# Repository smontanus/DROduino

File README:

DROduino
--------
DROduino is a prototype Digital ReadOut (DRO) system designed specifically for the
Taig Mini-Lathe. It is based on the Arduino UNO development board and utilizes high
resolution encoders to capture tool movement.

Author
------
Stephen S. Montanus
email: smont3780@gmail.com

License
-------
Creative Commons Attribution-ShareAlike 4.0 International Public License
(See LICENSE)

Files
-----
DROduino_v1_0.ino      Arduino sketch for reading and displaying rotary encoder data.
DROduino_v1.sch        Eagle schematic file.
DROduino_v1.brd        Eagle PCB board file.
DROduino_v1.0.fzz      Fritzing file

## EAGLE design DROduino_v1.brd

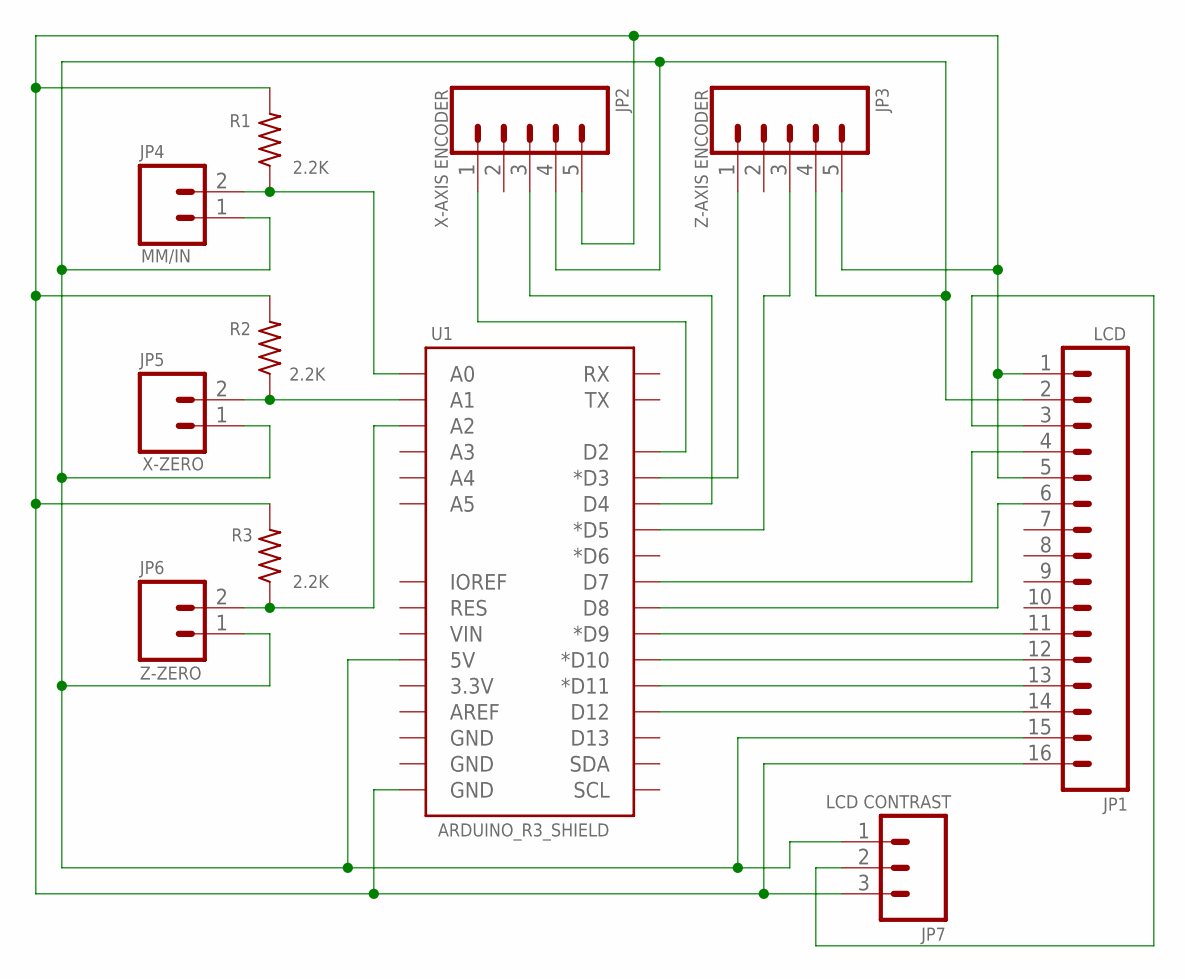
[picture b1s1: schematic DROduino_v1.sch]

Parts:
JP1: LCD; 1X16
JP2: X-AXIS ENCODER; 1X05
JP3: Z-AXIS ENCODER; 1X05
JP4: MM/IN; 1X02
JP5: X-ZERO; 1X02
JP6: Z-ZERO; 1X02
JP7: LCD CONTRAST; 1X03
R1, R2, R3: 2.2K; 0207/10
U1: ARDUINO_R3_SHIELD; UNO_R3_SHIELD

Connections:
unnamed: JP1.14, U1.D12
unnamed: JP1.13, U1.D11 (*D11)
unnamed: JP1.12, U1.D10 (*D10)
unnamed: JP1.11, U1.D9 (*D9)
unnamed: JP1.6, U1.D8
unnamed: JP1.4, U1.D7
unnamed: JP1.3, JP7.2
unnamed: JP2.1, U1.D2
unnamed: JP2.3, U1.D4
unnamed: JP3.1, U1.D3 (*D3)
unnamed: JP3.3, U1.D5 (*D5)
unnamed: JP1.1, JP1.5, JP1.16, JP2.5, JP3.5, JP7.3, R1.2, R2.2, R3.2, U1.GND@0 (GND)
unnamed: JP4.2, R1.1, U1.A0
unnamed: JP6.2, R3.1, U1.A2
unnamed: JP5.2, R2.1, U1.A1
unnamed: JP1.2, JP1.15, JP2.4, JP3.4, JP4.1, JP5.1, JP6.1, JP7.1, U1.5V

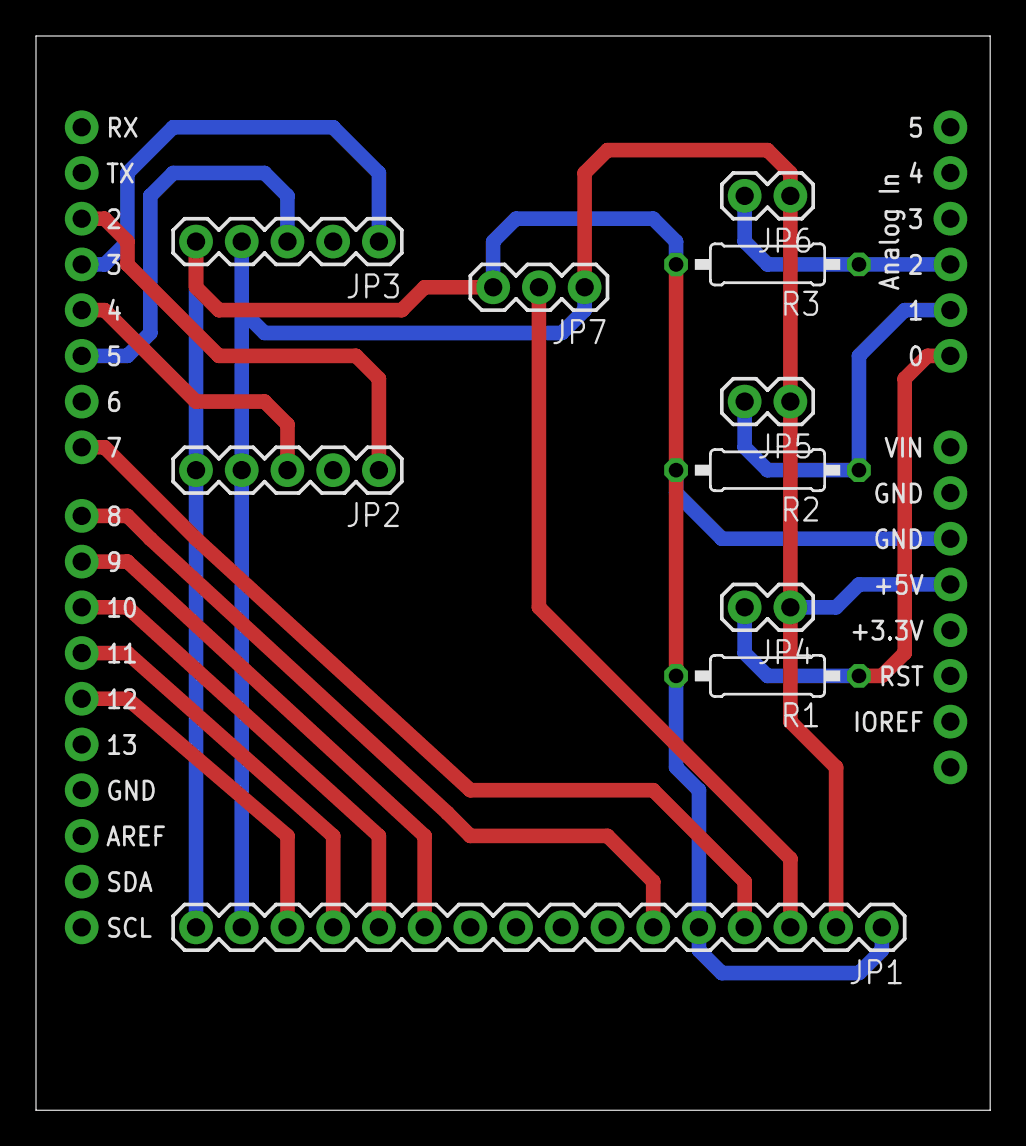
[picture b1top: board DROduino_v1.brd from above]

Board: 2 copper layers, 53.0 x 59.7 mm, 11 parts (0 on the bottom side), 16 nets.

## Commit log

2014-05-04 Initial Files
    Addition of the initial project files.
2015-03-14 Remarks
    Updated remarks in .ino file

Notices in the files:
parts and their libraries:
SparkFun-Boards: Licensing: CC v3.0 Share-Alike You are welcome to use this library for commercial purposes.
